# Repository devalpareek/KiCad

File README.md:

# Electrical circuit Sketches and PCB designs made using KiCad.

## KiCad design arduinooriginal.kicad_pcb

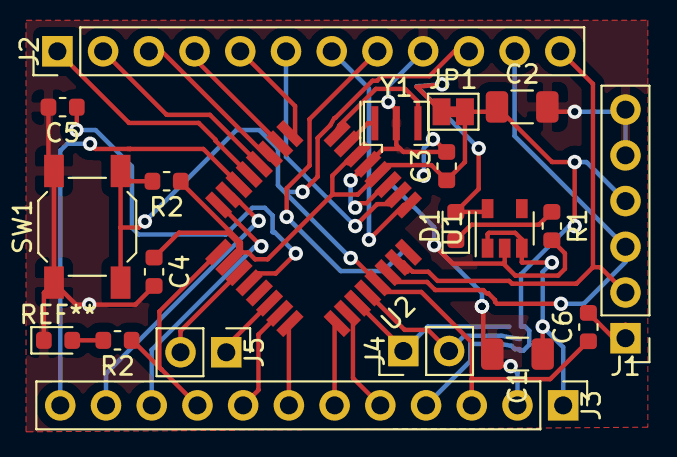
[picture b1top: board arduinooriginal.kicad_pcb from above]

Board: 2 copper layers, 20 parts (0 on the bottom side), 32 nets.

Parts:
C1, C2: 10u; C_1206_3216Metric
C3, C4, C5, C6: 0.1u; C_0603_1608Metric
D1: red; D_0603_1608Metric
J1: Conn_01x06; PinHeader_1x06_P2.54mm_Vertical
J2, J3: Conn_01x12; PinHeader_1x12_P2.54mm_Vertical
J4, J5: Conn_01x02; PinHeader_1x02_P2.54mm_Vertical
JP1: SolderJumper_2_Bridged; SolderJumper-2_P1.3mm_Bridged_Pad1.0x1.5mm
R1, R2, R2#2: 10k; R_0603_1608Metric
SW1: SW_SPST; SW_SPST_SKQG_WithoutStem
U1: MIC5205-2.5YM5; SOT-23-5
U2: ATmega328P-AU; atmeg328p-AU
Y1: Resonator_Small; Resonator_SMD_muRata_CSTxExxV-3Pin_3.0x1.1mm

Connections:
A0: J3.8, U2.23
A1: J3.7, U2.24
A2: J3.6, U2.25
A3: J3.5, U2.26
A4: J4.1, U2.27
A5: J4.2, U2.28
A6: J5.2, U2.19
A7: J5.1, U2.22
AREF: C5.1, U2.20
D2: J2.8, U2.32
D3: J2.7, U2.1
D4: J2.6, U2.2
D5: J2.5, U2.9
D6: J2.4, U2.10
D7: J2.3, U2.11
D8: J2.2, U2.12
D9: J2.1, U2.13
D10: J3.12, U2.14
DTR: C6.2, J1.1
GND: C1.2, C2.2, C3.2, C4.2, C5.2, J1.5, J1.6, J2.9, J3.2, R1.2, SW1.1, U1.2, U2.3, U2.5, Y1.2
MISO: J3.10, U2.16
MOSI: J3.11, U2.15
unnamed: D1.1, R1.1
unnamed: D1.2, JP1.1, U1.5
unnamed: U2.7, Y1.1
unnamed: U2.8, Y1.3
RAW: C1.1, J3.1, U1.1, U1.3
RESET: C6.1, J2.10, J3.3, R2#2.2, SW1.2, U2.29
RXI: J1.3, J2.11, U2.30
SCK: J3.9, R2.1, U2.17
TXO: J1.2, J2.12, U2.31
VCC: C2.1, C3.1, C4.1, J1.4, J3.4, JP1.2, R2#2.1, U2.4, U2.6, U2.18

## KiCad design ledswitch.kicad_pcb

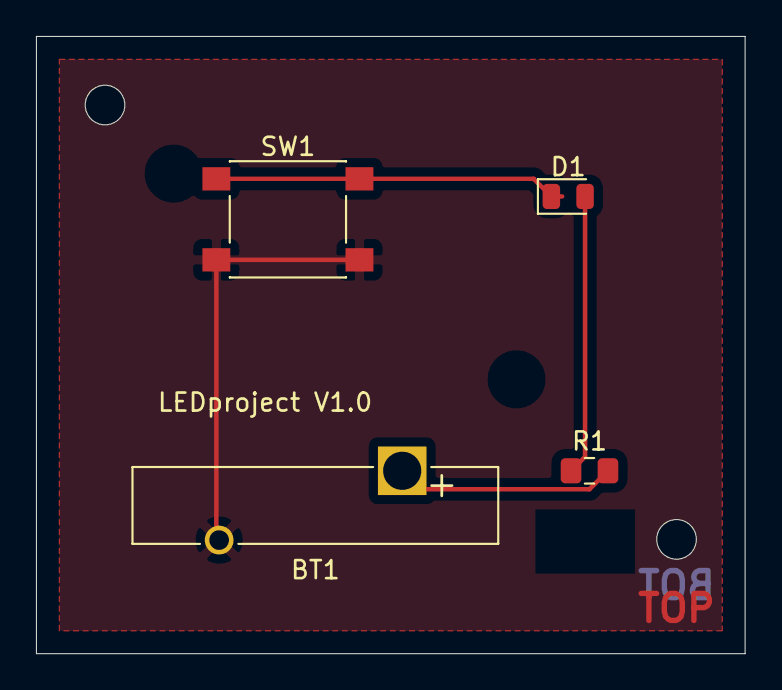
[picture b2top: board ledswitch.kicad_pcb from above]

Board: 2 copper layers, 39.4 x 34.3 mm, 4 parts (0 on the bottom side), 4 nets.

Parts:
BT1: Battery; Battery_Panasonic_CR2032-VS1N_Vertical_CircularHoles
D1: LED; LED_0805_2012Metric
R1: 1k; R_0805_2012Metric_Pad1.15x1.40mm_HandSolder
SW1: SW_Push; SW_Push_1P1T_NO_6x6mm_H9.5mm

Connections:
+5V: BT1.1, R1.2
GND: BT1.2, SW1.2
unnamed: D1.1, SW1.1
unnamed: D1.2, R1.1

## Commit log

2020-06-20 LED connected with battery and switch
    Using 5V battery, 1K resistor and PUSH switch.
2020-06-24 Arduino Pro mini
    Made using KiCad - Linux
